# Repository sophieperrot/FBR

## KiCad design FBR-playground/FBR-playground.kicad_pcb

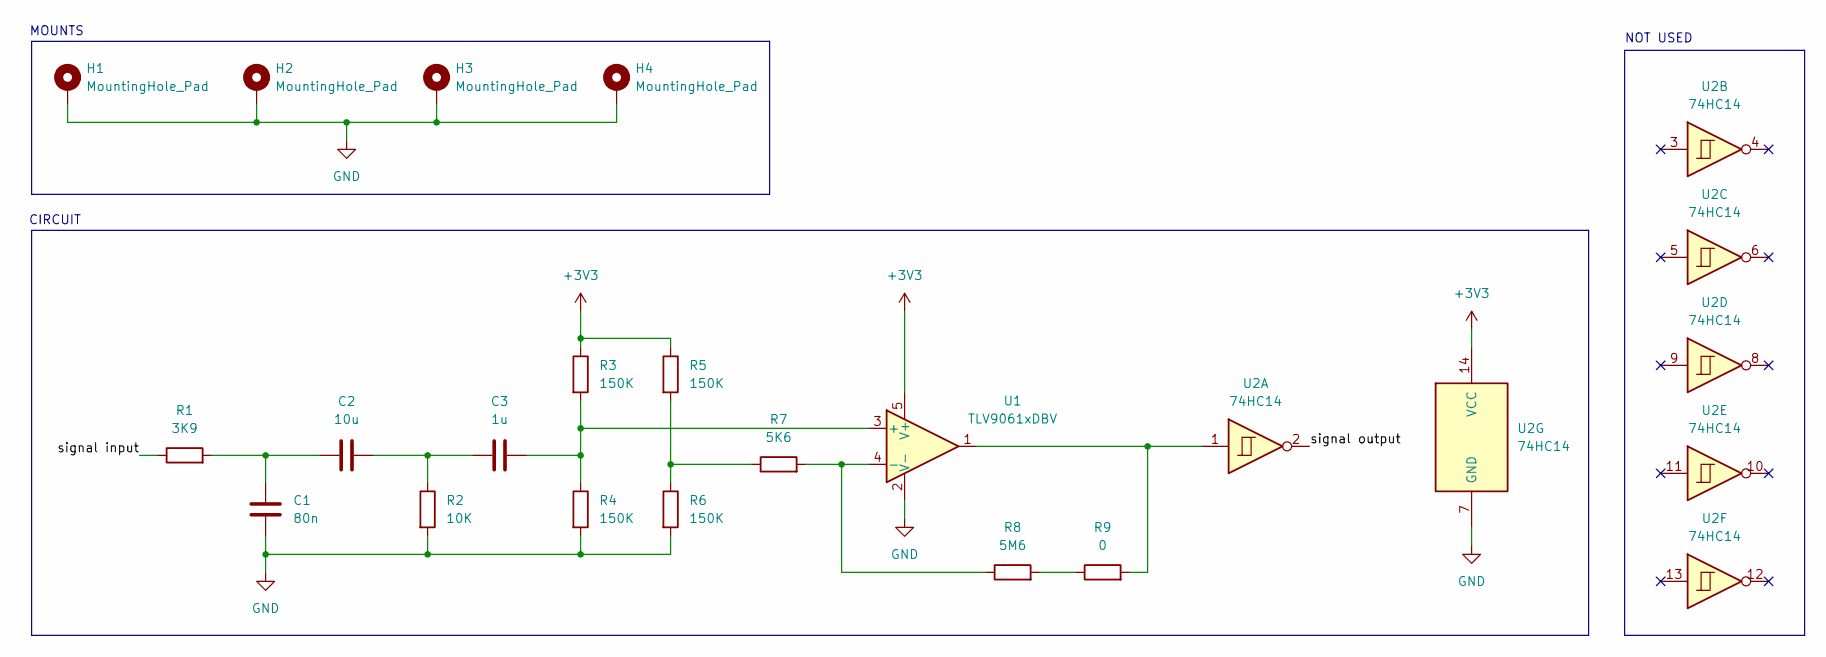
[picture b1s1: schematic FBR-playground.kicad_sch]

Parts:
C1: 80n; C_0805_2012Metric
C2: 10u; C_0805_2012Metric
C3: 1u; C_0805_2012Metric
H1, H2, H3, H4: MountingHole_Pad; MountingHole_2.7mm_M2.5_DIN965_Pad
R1: 3K9; R_0805_2012Metric
R2: 10K; R_0805_2012Metric
R3, R4, R5, R6: 150K; R_0805_2012Metric
R7: 5K6; R_0805_2012Metric
R8: 5M6; R_0805_2012Metric
R9: 0; R_0805_2012Metric
U1: TLV9061xDBV; SOT-23-5
U2: 74HC14; TSSOP-14_4.4x5mm_P0.65mm

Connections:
+3V3: R3.1, R5.1, U1.5 (V+), U2.14 (VCC)
/signal input: R1.1
/signal output: U2.2
GND: C1.1, H1.1 (1_1), H2.1 (1_1), H3.1 (1_1), H4.1 (1_1), R2.2, R4.2, R6.2, U1.2 (V-), U2.7 (GND)
unnamed: C1.2, C2.1, R1.2
unnamed: C2.2, C3.1, R2.1
unnamed: R5.2, R6.1, R7.1
unnamed: R8.2, R9.1
unnamed: R9.2, U1.1, U2.1
unnamed: C3.2, R3.2, R4.1, U1.3 (+)
unnamed: R7.2, R8.1, U1.4 (-)

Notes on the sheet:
CIRCUIT
NOT USED
MOUNTS

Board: 2 copper layers, 18 parts (0 on the bottom side), 9 nets, no tracks yet.
